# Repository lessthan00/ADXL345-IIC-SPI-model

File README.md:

# ADXL345  

## 模块1  
  
[模块1](https://item.taobao.com/item.htm?abbucket=14&id=665055929696&ns=1&priceTId=2100c82c17466082828256733e0be3&skuId=4968945735643&spm=a21n57.sem.item.81.3ed93903ScD7IM&utparam=%7B%22aplus_abtest%22%3A%22071eb1763aebb2fc6654ad566085d69f%22%7D&xxc=taobaoSearch)  
  
ADXL345是一款小而薄的超低功耗3轴加速度计，分辨率高（13位）今测量范围达士16g。数字输出数据为16位二进制补码格式，可通过SPI（3线或4线）或I2C数字接口访问。ADXL345非常适合移动设备应用。它可以在倾斜检测应用中测量静态重力加速度，还可以测量运动或冲击导致的动态加速度。其高分辨率（3.9mg/LSB），能够测量不到1.0°的倾斜角度变化  
  
ADXL345 三轴重力传感器模块  
  
参数:  
工作电压：DC3.3V/5V  
测量范围：土2/土4/土8/±16  
芯片工作温度：-40℃-80℃  
诸存温度：-40℃-105℃  
尺寸：28mmx14mm  
  
接口定义: 5V 3V3 GND VS CS  
SCL SDA SDO IN2 IN1  
  
接口定义:  
5V: 5V电源  
3V3: 3.3V电源  
GND:地  
Vs:电源电压  
CS:片选  
SCL: I2C串行时钟先/SPI时钟端  
SDA: 串行数据(I2C)/串行数据输入(SPI 4线)/串行数据输入和输出(SPI 3线)  
SDO: 串行数据输出(SPI 4线)/备用I2C地址选择(I2C)  
IN2: 中断2引脚  
IN1: 中断1引脚  
用户注意: 模块在I2C模式下的地址由SDO引脚决定  
  
有1117 LDO 转5V 为 3V3, 具有C1206_10uF*2 + C0805_100nF*2 滤波  
SCL SDA 使用10K上拉  
具有LED LED指示电源正常  
具有 XYZ轴指示

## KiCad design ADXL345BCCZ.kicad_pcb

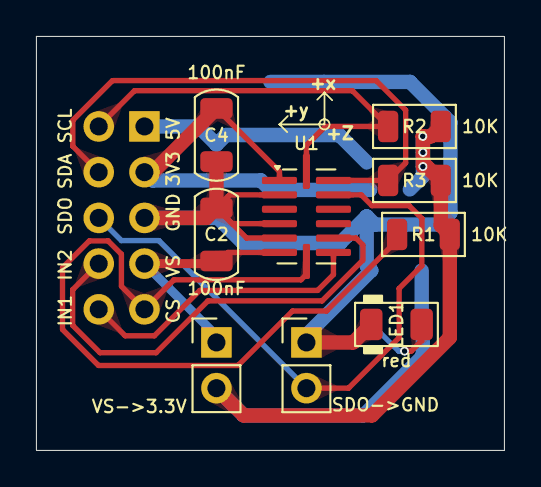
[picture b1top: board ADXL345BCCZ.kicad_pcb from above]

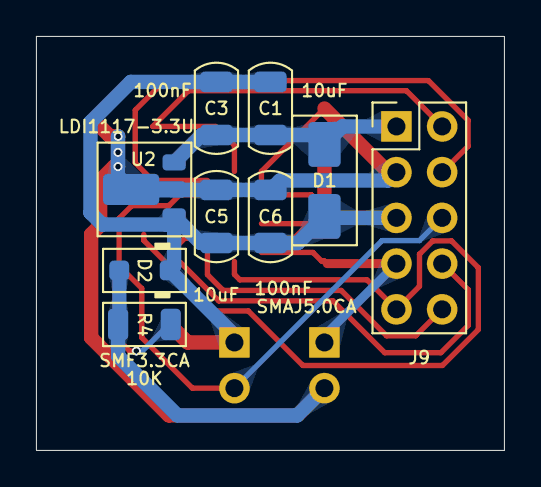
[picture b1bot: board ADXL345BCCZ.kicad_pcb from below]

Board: 2 copper layers, 26.0 x 23.0 mm, 18 parts (9 on the bottom side), 11 nets.

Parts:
C1, C5: 10uF; C_1206_3216Metric
C2, C3, C4, C6: 100nF; C_1206_3216Metric
D1: SMAJ5.0CA; D_SMA_TVS
D2: SMF3.3CA; D_SOD-123F
J3, J5: Conn_01x02; PinHeader_1x02_P2.54mm_Vertical
J9: Conn_02x05_Odd_Even; PinHeader_2x05_P2.54mm_Vertical
LED1: red; LED_1206_3216Metric
R1, R2, R3, R4: 10K; R_1206_3216Metric
U1: ADXL345; LGA-14_3x5mm_P0.8mm_LayoutBorder1x6y
U2: LDI1117-3.3U; SOT-89-3

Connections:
+3.3V: C4.1, C5.1, C6.1, D2.2 (A), J5.2, J9.3, R1.1, R2.1, R3.1, R4.1, U1.1 (Vdd_I/O), U2.2 (OUT)
+5V: C1.1, C3.1, D1.2 (A), J9.1, U2.3 (IN)
/CS: J9.9, R1.2, U1.7 (~CS)
/INT1: J9.10, U1.8 (INT1)
/INT2: J9.8, U1.9 (INT2)
/SCL: J9.2, R2.2, U1.14 (SCL/SCLK)
/SDA: J9.4, R3.2, U1.13 (SDA/SDI/SDIO)
/SDO: J3.2, J9.6, U1.12 (SDO/ADDR)
/VS: C2.1, J5.1, J9.7, U1.6 (Vs)
GND: C1.2, C2.2, C3.2, C4.2, C5.2, C6.2, D1.1 (K), D2.1 (K), J3.1, J9.5, LED1.1 (K), U1.2 (GND), U1.4 (GND), U1.5 (GND), U2.1
unnamed: LED1.2 (A), R4.2
